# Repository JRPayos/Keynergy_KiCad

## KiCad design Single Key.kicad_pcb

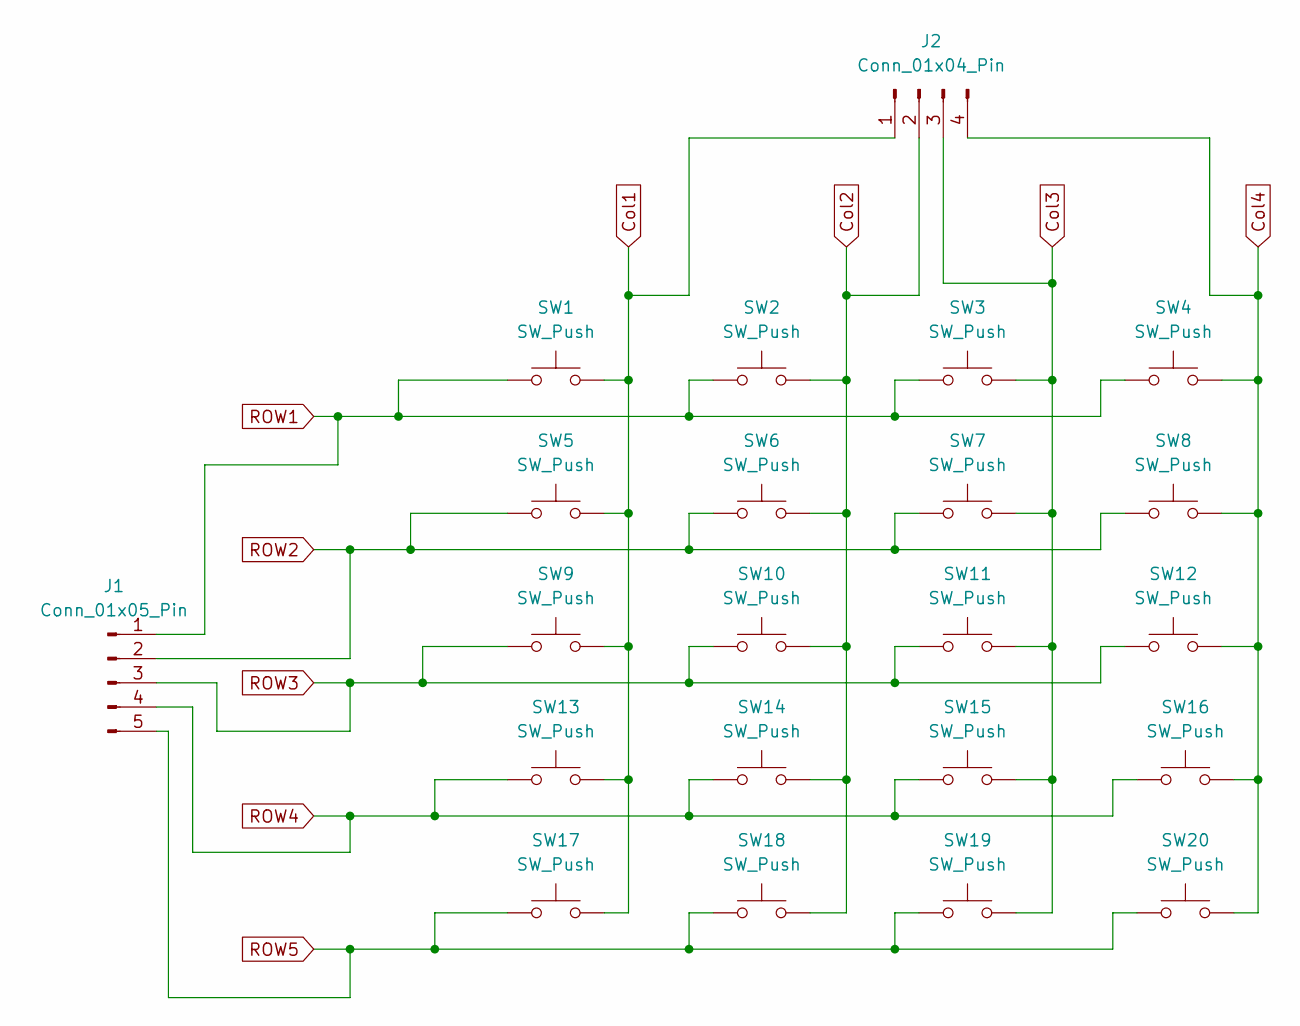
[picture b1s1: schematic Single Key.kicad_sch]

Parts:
J1: Conn_01x05_Pin; PinHeader_1x05_P2.54mm_Vertical
J2: Conn_01x04_Pin; PinSocket_1x04_P2.54mm_Vertical
SW1, SW2, SW3, SW4, SW5, SW6, SW7, SW8, SW9, SW10, SW11, SW12, SW13, SW14, SW15, SW16, SW17, SW18, SW19, SW20: SW_Push; SW_PUSH_6mm

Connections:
Col1: J2.1, SW1.2, SW5.2, SW9.2, SW13.2, SW17.2
Col2: J2.2, SW2.2, SW6.2, SW10.2, SW14.2, SW18.2
Col3: J2.3, SW3.2, SW7.2, SW11.2, SW15.2, SW19.2
Col4: J2.4, SW4.2, SW8.2, SW12.2, SW16.2, SW20.2
ROW1: J1.1, SW1.1, SW2.1, SW3.1, SW4.1
ROW2: J1.2, SW5.1, SW6.1, SW7.1, SW8.1
ROW3: J1.3, SW9.1, SW10.1, SW11.1, SW12.1
ROW4: J1.4, SW13.1, SW14.1, SW15.1, SW16.1
ROW5: J1.5, SW17.1, SW18.1, SW19.1, SW20.1

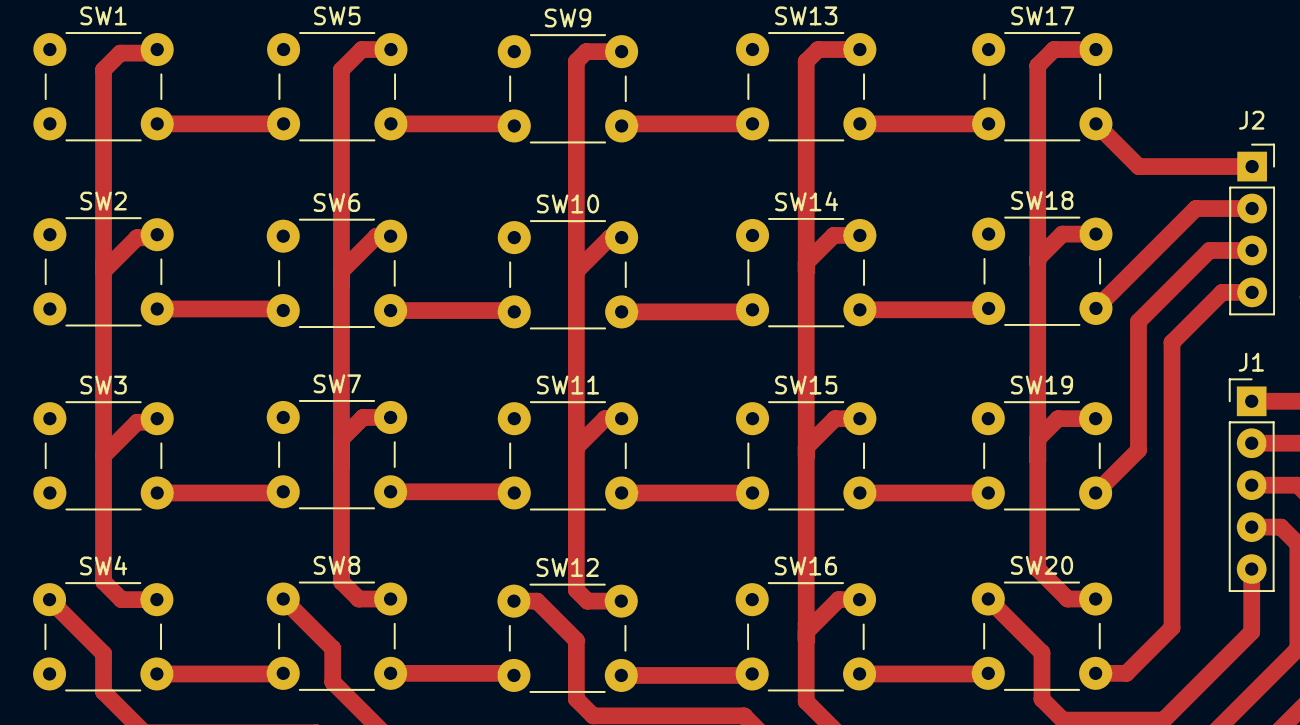
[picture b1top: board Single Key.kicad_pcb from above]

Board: 2 copper layers, 22 parts (0 on the bottom side), 9 nets.

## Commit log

2025-03-25 Added new files
2025-03-28 New Files
2025-03-28 new update
2025-03-28 new updates

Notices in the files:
Single Key.kicad_pcb:
© JR Payos
